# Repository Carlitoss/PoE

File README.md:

PoE
===

PoE Extractor with regulable output voltages.

More info: [Carlitosspedia](http://www.carlitosspedia.info)

[www.carlitosspedia.info](http://www.carlitosspedia.info)

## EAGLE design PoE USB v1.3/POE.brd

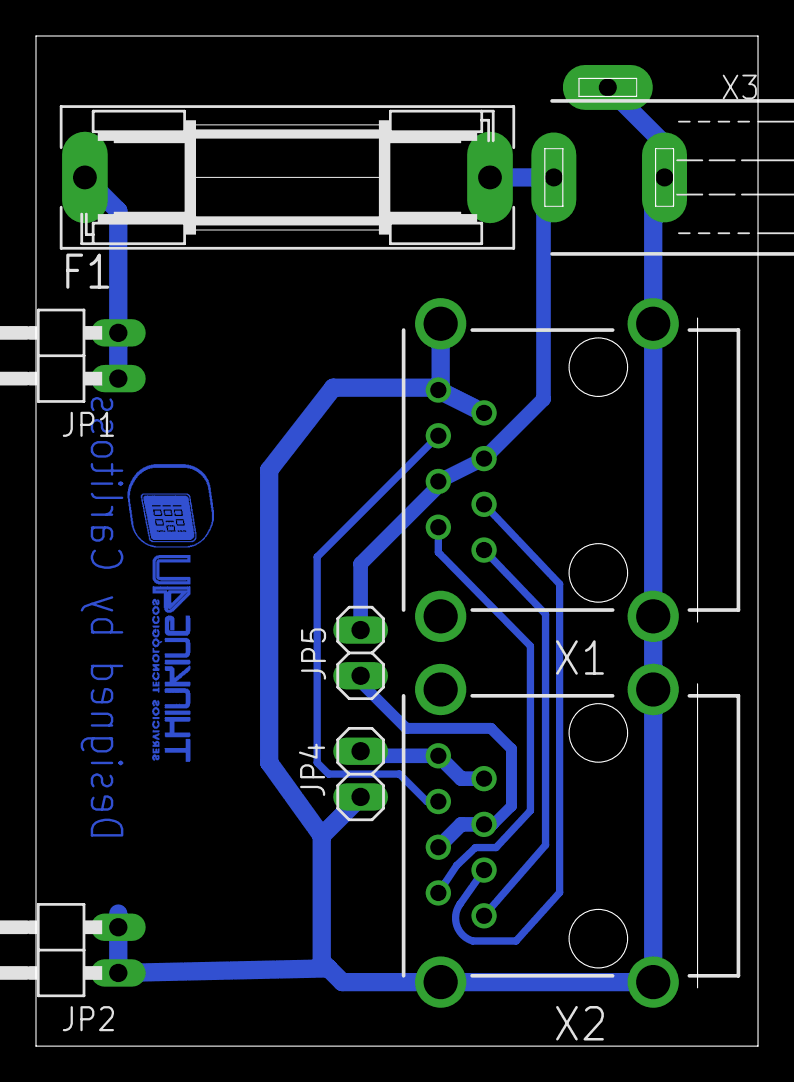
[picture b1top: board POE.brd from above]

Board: 2 copper layers, 40.1 x 56.1 mm, 8 parts (0 on the bottom side), 9 nets.

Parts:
F1: SH22,5
JP1, JP2: 1X02/90
JP4, JP5: 1X02
X1, X2: RJ45-6L21-B; RJ45-SHIELD1
X3: 733980-62

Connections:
GND: JP2.1, JP2.2, JP4.1, X1.7, X1.8, X1.S1, X1.S2, X1.S4, X2.S1, X2.S2, X2.S3, X3.2, X3.3
unnamed: F1.1, JP1.1, JP1.2
unnamed: X1.6, X2.6
unnamed: X1.3, X2.3
unnamed: X1.2, X2.2
unnamed: X1.1, X2.1
unnamed: F1.2, JP5.1, X1.4, X1.5, X3.1
unnamed: JP4.2, X2.7, X2.8
unnamed: JP5.2, X2.4, X2.5

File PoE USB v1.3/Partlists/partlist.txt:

Partlist

Exported from POE.sch at 12/04/2013 17:29:55

EAGLE Version 6.4.0 Copyright (c) 1988-2013 CadSoft

Assembly variant: 

Part     Value          Device       Package      Library             Sheet

F1                      SH22,5       SH22,5       fuse                1
JP1                     PINHD-1X2/90 1X02/90      pinhead             1
JP2                     PINHD-1X2/90 1X02/90      pinhead             1
JP4                     PINHD-1X2    1X02         pinhead             1
JP5                     PINHD-1X2    1X02         pinhead             1
X1       RJ45-6L21-B    RJ45-6L21-B  RJ45-SHIELD1 con-tycoelectronics 1
X2       RJ45-6L21-B    RJ45-6L21-B  RJ45-SHIELD1 con-tycoelectronics 1
X3                      733980-62    733980-62    con-conrad          1

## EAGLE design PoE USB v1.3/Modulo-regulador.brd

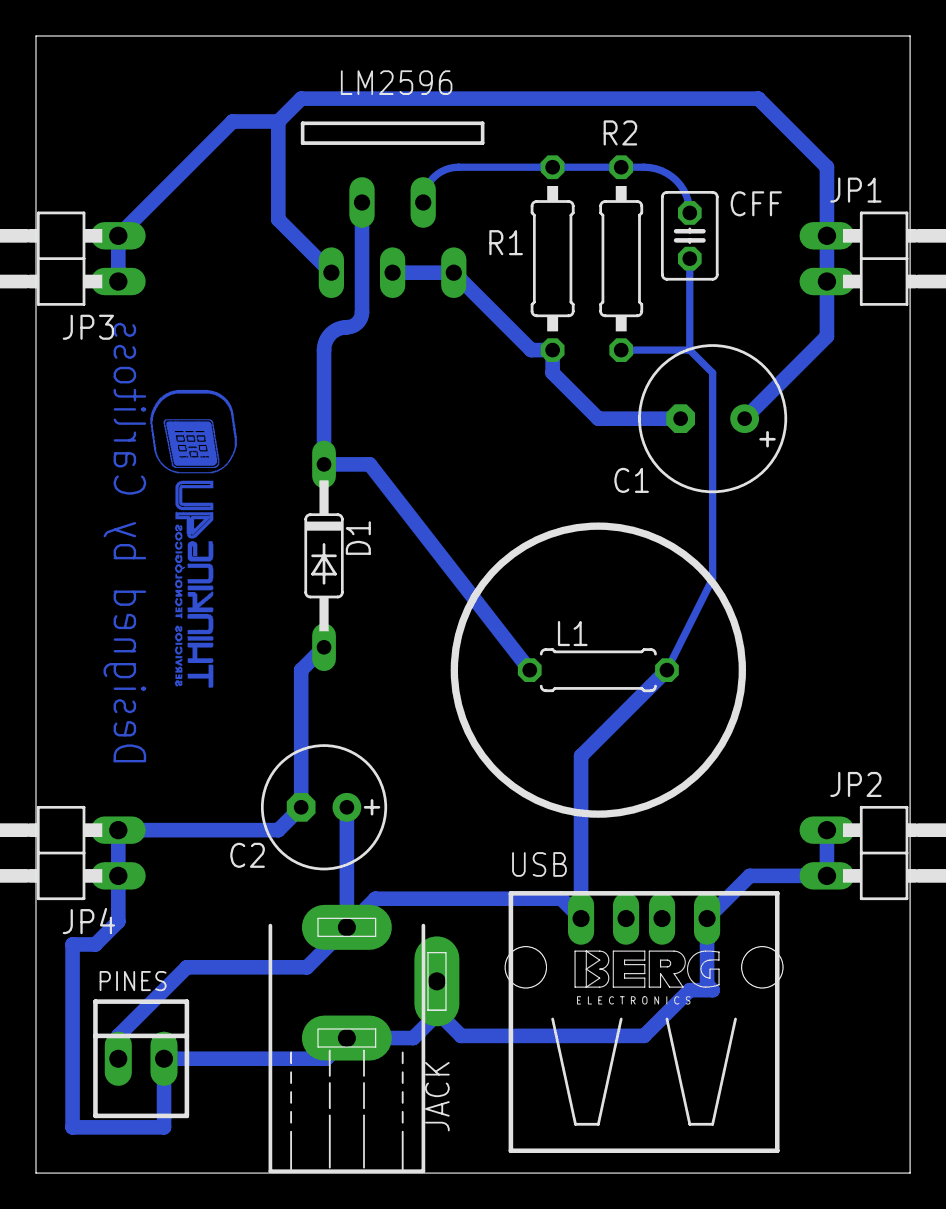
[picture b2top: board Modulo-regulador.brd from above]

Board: 2 copper layers, 48.6 x 63.2 mm, 15 parts (0 on the bottom side), 5 nets.

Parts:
C1: 470uF; E3,5-8
C2: 220uF; E2,5-7
CFF: C025-030X050
D1: 1N5825; DO35-10
JACK: 733980-62
JP1, JP2, JP3, JP4: 1X02/90
L1: 47uH; 0207/7
LM2596: TO220-51
PINES: 22-23-2021
R1: 1K; 0207/10
R2: 0207/10
USB: PN87520

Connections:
GND: C1.-, C2.-, D1.A, JACK.2, JACK.3, JP2.1, JP2.2, JP4.1, JP4.2, LM2596.3, LM2596.5, PINES.2, R1.2, USB.4
unnamed: D1.C, L1.1, LM2596.2
unnamed: C1.+, JP1.1, JP1.2, JP3.1, JP3.2, LM2596.1
unnamed: CFF.1, LM2596.4, R1.1, R2.1
V+: C2.+, CFF.2, JACK.1, L1.2, PINES.1, R2.2, USB.1

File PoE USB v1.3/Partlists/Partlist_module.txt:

Partlist

Exported from Modulo-regulador.sch at 12/04/2013 17:30:35

EAGLE Version 6.4.0 Copyright (c) 1988-2013 CadSoft

Assembly variant: 

Part     Value          Device          Package      Library    Sheet

C1       470uF          CPOL-EUE3.5-8   E3,5-8       rcl        1
C2       220uF          CPOL-EUE2.5-7   E2,5-7       rcl        1
CFF                     C-EU025-030X050 C025-030X050 rcl        1
D1       1N5825         BAT19           DO35-10      diode      1
JACK                    733980-62       733980-62    con-conrad 1
JP1                     PINHD-1X2/90    1X02/90      pinhead    1
JP2                     PINHD-1X2/90    1X02/90      pinhead    1
JP3                     PINHD-1X2/90    1X02/90      pinhead    1
JP4                     PINHD-1X2/90    1X02/90      pinhead    1
L1       47uH           L-EU0207/7      0207/7       rcl        1
LM2596                  LM2596TV        TO220-51     linear     1
PINES    22-23-2021     22-23-2021      22-23-2021   con-molex  1
R1       1K             R-EU_0207/10    0207/10      rcl        1
R2                      R-EU_0207/10    0207/10      rcl        1
USB                     PN87520         PN87520      con-berg   1

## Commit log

2013-04-12 Punto de partida de ambas versiones
2013-04-12 Actualización de directorios
2013-04-12 PoE Modular acabado
    Acabada la extracción o inyección de Power
2013-04-12 Ver 1.1 of the modular system
2013-04-12 Partlists added
2013-04-15 Arranged items and deleted backups
2013-11-04 Modified README.md
